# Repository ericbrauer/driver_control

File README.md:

# driver_control
PCB Design for ETD555 group project

This repository includes the design files created for a motor driver circuit. 
This PCB connected to a LabJack UE-9 and was manipulated via Python code.

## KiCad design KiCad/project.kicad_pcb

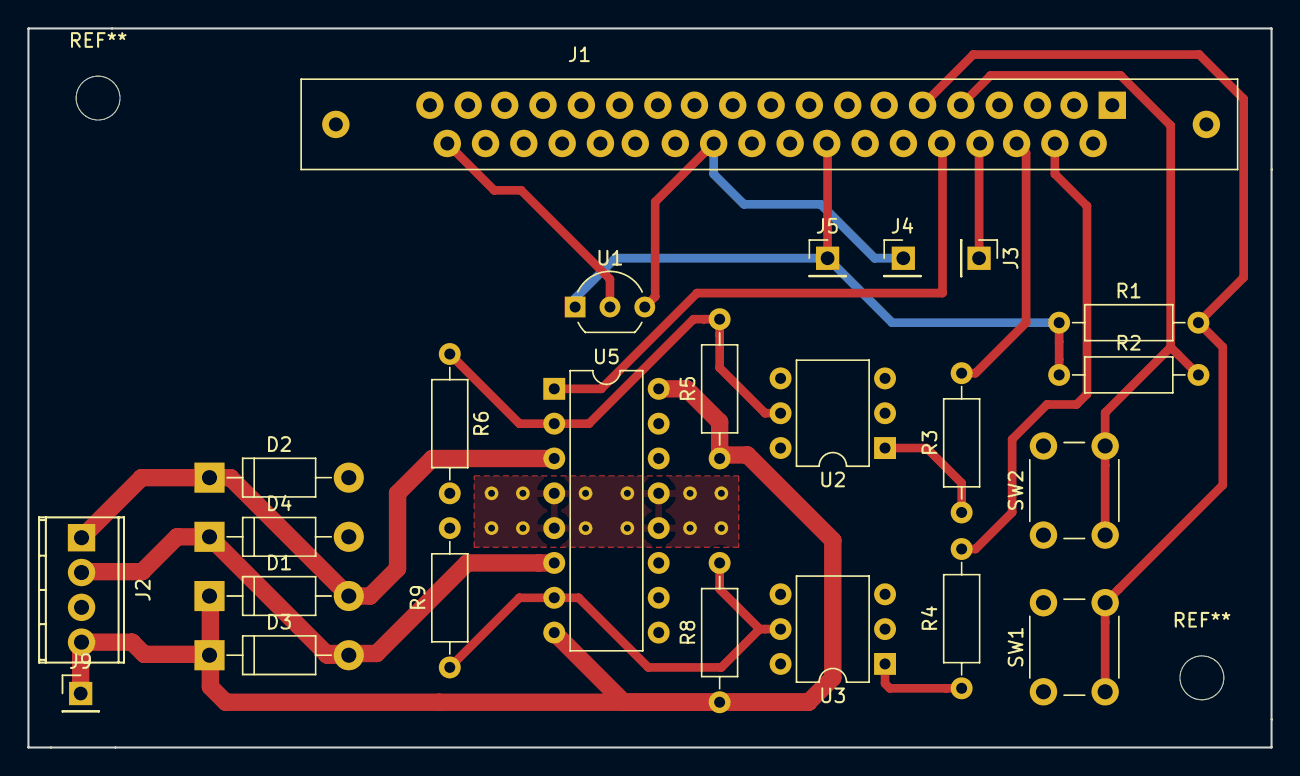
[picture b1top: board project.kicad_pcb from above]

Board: 2 copper layers, 90.7 x 52.5 mm, 24 parts (0 on the bottom side), 17 nets.

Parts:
D1, D2, D3, D4: D; D_DO-41_SOD81_P10.16mm_Horizontal
J1: DB37_MALE; DB37FD
J2: CONN_01X04; TerminalBlock_Pheonix_MPT-2.54mm_4pol
J3: CONN_01X01; Socket_Strip_Straight_1x01_Pitch2.54mm
J4, J5, J9: TEST_1P; Socket_Strip_Straight_1x01_Pitch2.54mm
R1, R2, R5, R6, R8, R9: 10k; R_Axial_DIN0207_L6.3mm_D2.5mm_P10.16mm_Horizontal
R3, R4: 220; R_Axial_DIN0207_L6.3mm_D2.5mm_P10.16mm_Horizontal
SW1, SW2: Tact_SW_NO; SW_PUSH_6mm
U1: LM35DZ; TO-92_Inline_Wide
U2, U3: 4N25; DIP-6_W7.62mm
U5: L293D; DIP-16_W7.62mm

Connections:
+5V: J1.27, J5.1, R1.1, R2.1, U1.1
+12V: D1.1, D3.1, J2.4, J9.1, R5.1, R8.1, U5.8, U5.16
/Driver Circuit alternate/DIRECTION1: J1.22, R3.2
/Driver Circuit alternate/DIRECTION2: J1.21, R4.2
/Driver Circuit alternate/ENABLE: J1.24, U5.1
/Driver Circuit alternate/MOTOR1: D1.2, D2.1, J2.1, U5.3
/Driver Circuit alternate/MOTOR2: D3.2, D4.1, J2.2, U5.6
/Inputs/RESET: J1.5, R2.2, SW2.2
/Inputs/STOP: J1.6, R1.2, SW1.2
/Inputs/TEMPERATURE: J1.37, U1.2
GND: D2.2, D4.2, J2.3, R6.2, R9.2, U2.4, U3.4, U5.4, U5.5, U5.12, U5.13
GNDREF: J1.1, J1.8, J1.10, J1.19, J1.30, J4.1, SW1.1, SW2.1, U1.3, U2.2, U3.2
unnamed: J1.23, J3.1
unnamed: R3.1, U2.1
unnamed: R4.1, U3.1
unnamed: R5.2, R6.1, U2.5, U5.2
unnamed: R8.2, R9.1, U3.5, U5.7

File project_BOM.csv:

"Id";"Designator";"Package";"Quantity";"Designation";"Supplier and ref";
1;"REF**,REF**,REF**,REF**,REF**,REF**,REF**,REF**,REF**,REF**,REF**,REF**";"0.5mm_VIA";12;"0.5mm_VIA";;;
2;"J1";"DB37FD";1;"DB37_MALE";;;
3;"J2";"TerminalBlock_Pheonix_MPT-2.54mm_4pol";1;"CONN_01X04";;;
4;"SW1,SW2";"SW_PUSH_6mm";2;"Tact_SW_NO";;;
5;"U1";"TO-92_Inline_Wide";1;"LM35DZ";;;
6;"U2,U3";"DIP-6_W7.62mm";2;"4N25";;;
7;"D1,D2,D3,D4";"D_DO-41_SOD81_P10.16mm_Horizontal";4;"D";;;
8;"J4,J5,J9";"Socket_Strip_Straight_1x01_Pitch2.54mm";3;"TEST_1P";;;
9;"R1,R2,R5,R6,R8,R9";"R_Axial_DIN0207_L6.3mm_D2.5mm_P10.16mm_Horizontal";6;"10k";;;
10;"R3,R4";"R_Axial_DIN0207_L6.3mm_D2.5mm_P10.16mm_Horizontal";2;"220";;;
11;"U5";"DIP-16_W7.62mm";1;"L293D";;;
12;"J3";"Socket_Strip_Straight_1x02_Pitch2.54mm";1;"CONN_01X02";;;
13;"REF**,REF**";"MountingHole_3.2mm_M3";2;"MountingHole_3.2mm_M3";;;

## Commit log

2018-01-24 uploading project files to github
2018-01-25 changed filename
2018-01-25 fixed a link
2018-01-25 Final fix to image path for readme
